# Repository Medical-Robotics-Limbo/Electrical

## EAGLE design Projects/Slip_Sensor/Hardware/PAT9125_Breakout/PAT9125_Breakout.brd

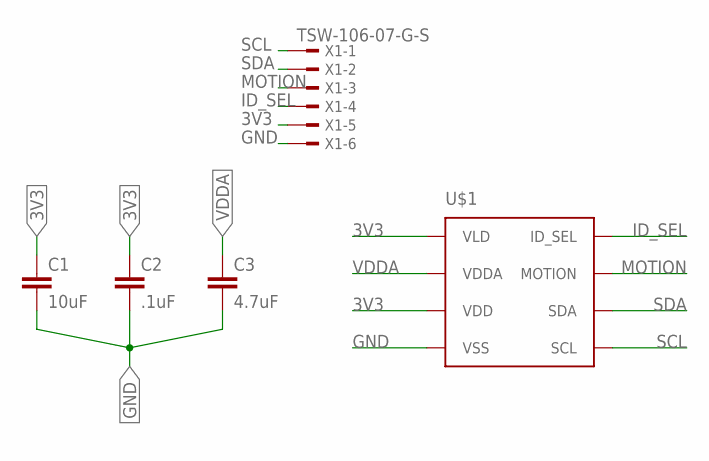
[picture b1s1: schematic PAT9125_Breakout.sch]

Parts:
C1: 10uF; C0603
C2: .1uF; C0603
C3: 4.7uF; C0603
U$1: PAT9125EL
X1: TSW-106-07-G-S; TSW-106-XX-G-S

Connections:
3V3: C1.1, C2.1, U$1.P$1 (VLD), U$1.P$3 (VDD), X1.5
GND: C1.2, C2.2, C3.2, U$1.P$4 (VSS), X1.6
ID_SEL: U$1.P$8 (ID_SEL), X1.4
MOTION: U$1.P$7 (MOTION), X1.3
SCL: U$1.P$5 (SCL), X1.1
SDA: U$1.P$6 (SDA), X1.2
VDDA: C3.1, U$1.P$2 (VDDA)

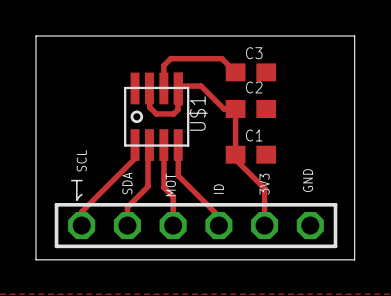
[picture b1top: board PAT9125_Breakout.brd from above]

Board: 2 copper layers, 17.7 x 12.4 mm, 5 parts (0 on the bottom side), 7 nets.

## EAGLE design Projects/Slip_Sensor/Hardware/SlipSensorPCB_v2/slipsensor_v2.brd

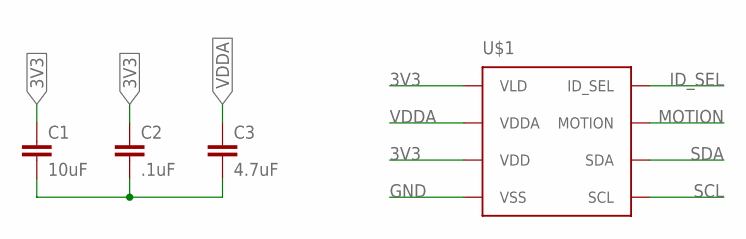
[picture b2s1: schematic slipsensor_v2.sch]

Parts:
C1: 10uF; C0402
C2: .1uF; C0402
C3: 4.7uF; C0402
U$1: PAT9125EL

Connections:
3V3: C1.1, C2.1, U$1.P$1 (VLD), U$1.P$3 (VDD)
GND: C1.2, C2.2, C3.2, U$1.P$4 (VSS)
ID_SEL: U$1.P$8 (ID_SEL)
MOTION: U$1.P$7 (MOTION)
SCL: U$1.P$5 (SCL)
SDA: U$1.P$6 (SDA)
VDDA: C3.1, U$1.P$2 (VDDA)

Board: 2 copper layers, 4 parts (0 on the bottom side), 3 nets, no tracks yet.

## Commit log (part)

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2021-12-27 Transferred all files from gatech GitHub
2022-02-12 Fixed PAT9125EL footprint
2022-02-12 Created git ignore for eagle files
2022-02-17 Added multiplexer library
2022-02-21 Added MCU research excel sheet
2022-02-22 changed function names multiplexor
2022-02-22 minor changes
2022-02-24 signal acquisition with amplification LTSpice
2022-02-24 changed signal acquisition opamp
2022-02-24 Reorganized EMG sensor folders into distinct stages
2022-02-24 Auto stash before revert of "Reorganized EMG sensor folders into distinct stages"
2022-02-24 Rebased
2022-02-24 Separated EMG folders
2022-02-24 Added git ignore for LTSpice and MacOS files
2022-03-01 created ADC parts sheet
2022-03-03 Added Mac symlink gen
2022-03-04 Added code to make slip sensor throw error if not connected on setup
2022-03-08 added eagle libraries documentation
2022-03-08 added breakout board schematic for pat9125 slip sensor
2022-03-08 added fsr to eagle libraries
2022-03-10 added RP2040 IC symbol/footprint
2022-03-13 Added FSR resistor calculator
2022-03-15 The changes I made to the PAT9125 breakout board.
2022-03-15 finalized PAT9125 breakout board for ordering
2022-03-29 minor fixes to slip sensor code
2022-03-30 Added rectification ltspice thang - sharty
2022-03-30 Added rectification ltspice thang
2022-04-06 Transfer palm hub ADC schematic
2022-04-06 Added op amp rectification sir-kit
2022-04-07 Uploaded working PAT9125EL code
2022-04-13 setup pins for ADC108 testing script
2022-04-13 attempt SPI reading from ADC
2022-04-13 fixed SPI function call
2022-04-17 Updated rectification circuit
2022-04-21 Update tested ADC SPI data transfer
2022-09-26 Update palm hub test code - separate channel input from data transfer
2022-10-03 Add files via upload
    Code to test controlling the intensity of vibrations from the vibration motor. Includes functions for various pulses.
2022-11-02 Added Potentiometer Position sensing code
2022-11-02 uploaded pico slip sensor test
2022-11-02 Update pot test to include motor feedback loop
    Not yet working, only saves initial pot values
2022-11-14 Create palmhub_KiCad_Naveen (v1)
2022-11-15 Motor Controll Added
2022-12-01 Update Pot Code
2023-02-20 New slipsensor folder
    PAT files are moved to the slipsensor folder and the two slipsensor files are seperated to different folders
2023-03-02 Arduino update serial plotter
    New code on arduino allows to plot the magnitude.
2023-03-08 Code Resets dx and dy to 0
    When there is no shear force, the code resets dx and dy to 0.
2023-03-29 Added seperate file for motor controller testing
2023-04-17 Added single finger motor control to wait for EMG
2023-04-17 Added motor control code for emg side
2023-05-08 WIP: Motor w/ built in Encoder
2023-09-18 Added Seth's EMG PCB work
2023-09-20 Add ADC interrupt code
2023-09-20 Add I2C helper write/read functions
2023-09-20 Add BioTac Product Manual
    electrical schematics and other very important information.
2023-10-04 Testing encoder
2023-10-25 Testing board issues
2023-11-28 PWM control, pid
2024-03-27 new schematic upload
2024-09-18 Added initial files
2024-09-18 Added some footprints
2024-09-23 Added footprints for molex connectors
2024-09-23 Added all footprints
2024-09-25 Added imported footprints and symbols to the project folder
2024-09-26 Created preliminary PCB layout
2024-09-30 Added PCB traces.
2024-10-01 Generated Gerber Files and Drill File
2024-10-21 Create MedRobo_EncoderTest1.ino
    Arduino sketch for encoder version 1
2025-02-18 Test
    Testing whether Github can recognize my changes
2025-02-18 Added Arduino Code and removed test
2025-03-26 Update schematic and layout
2025-09-22 9/22 pcb
